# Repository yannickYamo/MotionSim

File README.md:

# MotionSim

MotionSim is an open-source simulator for motor drives. Give it a power transistor from any semiconductor manufacturer, a motor and a load, and it tells you what the part loses, how hot it runs and whether it holds. One physical model covers the whole drive: the switching edges, the losses and the junction temperature, the mains front end, the motor, and the control loop down to its C code.

[Try it in your browser](https://yannickyamo.github.io/MotionSim/): nothing to install, no account, and nothing you enter leaves the page.

## Everything in one place

A drive is usually designed in pieces: a loss calculator from each semiconductor manufacturer, a circuit simulator for the stage, a control toolbox for the loop, and a spreadsheet to hold them together. Each has its own model, and none knows what the others assumed.

MotionSim is one tool and one simulation, from the circuit to the code:

- **Choose the part.** Any manufacturer's transistor, modelled from its own datasheet and compared on your duty.
- **Design the stage.** Losses, junction temperatures, gate drive, DC link and the mains front end.
- **Match the motor.** Seven kinds of motor, each run through its real load from start-up until the heatsink is warm.
- **Find the best control.** Twenty-four schemes, tuned for your motor, simulated switch by switch and compared on what they cost the power stage.
- **Export the code.** The control law as C, checked against the simulation, for your microcontroller.

Change one figure and every answer follows, because it is the same model all the way down.

## The infrastructure

One engine carries a design from the datasheet to the microcontroller. Each layer feeds the next, so a change anywhere moves every answer.

| Layer | What it does |
|---|---|
| **Device models** | Built from the part's own datasheet, each value with its page. IGBT, silicon, SiC and GaN, from any manufacturer, on the same terms. |
| **Loss and thermal engine** | Conduction, switching and junction temperature, solved together, through the application's real duty from start-up until the heatsink is warm. |
| **Front end** | The stage between the mains and the DC link, chosen for the design and counted in its losses. |
| **Control lab** | Twenty-four control schemes, tuned for your motor and simulated switch by switch. |
| **Export** | The control law as C, proved against the simulation, for the microcontroller you pick. |

It runs where you work: in the browser with nothing to install, on your own machine for your own datasheets, from a terminal, or driven by your coding agent.

## The journey

Five steps, one page, the power stage drawn on screen the whole time.

1. **The part.** Drop a datasheet, type a few of its figures, or pick an example.
2. **The motor.** Proposed from the part, yours to change.
3. **The supply.** A battery, a DC supply or the AC mains.
4. **The load.** A washing machine, a compressor, a vehicle, a robot joint, or your own profile.
5. **The answer.** Passes, ruled out, or undecided on this data, with what limits the part and what to change.

From there, open the control lab, close the loop and take the code.

### One design, start to finish

*A 1200 V SiC module, an eight-pole interior-magnet motor, an 800 V battery: can it drive an electric car, and what is the best way to control it?* The part is made up; every figure and graph below is the tool's own.

**1. The verdict.** Passes. At 4500 rpm and 156 N·m the six switches lose 369 W, 220 W of it in switching, at 98.4 % efficiency with the motor's windings. The hottest junction is 82 °C, at standstill, and the part would carry 1.74 times this load.

**2. The drive cycle.** Town, main road, a hill, and town again. The junction is followed through all of it, with the worst swing marked, and braking puts 3.73 MJ back in the battery.

**3. One switching edge.** Press a spike on the loss chart and the turn-off opens as an oscilloscope would show it: 132 A cut off, the voltage overshooting to 895 V on an 800 V link, then ringing out. The turn-on sits beside it, with di/dt, dv/dt and the energy of each.

**4. The control.** The control lab opens on torque control with least current and field weakening, every gain tuned for this motor, and runs it switch by switch. It passes, and points at the switching loss: a modulation that clamps each leg at its current peak would cut it.

**5. A better scheme.** Pick the traction scheme with the clamp placed for least switching loss and run again: 255 W in place of 369 W, the switching loss halved to 113 W and the junction 4 K cooler, with the current's distortion going from 1.77 % to 2.24 %.

**6. The loop, in frequency.** The Laplace lens gives the same loop its Bode plot, margins, step and poles: 62.8° of phase margin, 10 dB of gain margin, a 2.25 kHz bandwidth.

**7. The code.** Export the scheme as C, with a replay that checks it against the run.

## Outcomes

- **A part chosen on your own duty.** Up to five parts, from any manufacturers, side by side.
- **An answer you can stand behind.** Every figure opens on its equation and its datasheet page. Where the datasheet cannot settle it, you are told what to measure.
- **Thermal trouble found before the prototype.** The hottest moment of the real duty, and the life that cycling leaves.
- **A drive, not only a part.** The front end, the tuned control and the C that runs it, from the same design.

## Built for AI agents

MotionSim runs an MCP server beside the page. Connect Claude Code, or any MCP client, and your agent works on the same design you see:

```
claude mcp add --transport http motionsim http://localhost:4310/mcp --header "Authorization: Bearer <code>"
```

- **It reads what you see.** The design, the results, the scheme's blocks and gains, the loop margins and the traces of the last run.
- **It does what you do.** Chooses a part, changes a figure, switches the scheme, retunes a gain, runs a test or a sweep, exports the report and the C.
- **You stay in control.** Every change shows on your page as it happens, with **Undo**, and is listed in the agent's activity.

Ask it to review the design, to tune the current loop for more phase margin, or to find the lowest-loss scheme. The server runs on your machine only. With no page at all, `motionsim agent` prints the guide for driving MotionSim from a terminal. See [docs/MCP.md](https://github.com/yannickYamo/MotionSim/blob/main/docs/MCP.md).

## Your own parts

The live page takes the few figures you type from a datasheet. To have the PDF read for you, and to open the control lab, run MotionSim on your own machine:

```
uvx --from git+https://github.com/yannickYamo/MotionSim motionsim serve
```

The datasheet is read by a language model you choose, with your own key, or by one you host. The project runs no server: your files go from your machine to your model and nowhere else.

From a terminal, with no datasheet and no key:

```
motionsim simulate example --vdc 300 --irms 10 --m 0.9 --pf 0.85 --fsw 8000 --tsink 60
```

```
made-up 600 V IGBT (Si IGBT)
  switch   conduction    4.602 W
           turn-on       0.888 W
           turn-off      0.708 W
  diode    conduction    1.079 W
           recovery      0.286 W
  power-stage loss       45.37 W
  efficiency             98.17 %
  Tj switch  average      80.9 °C   peak   85.4 °C
  Tj diode   average      76.9 °C   peak   79.1 °C
  T case                  64.5 °C
  margin to Tj max        45.3 °C
  hottest junction        76.9 to 104.7 °C across the thermal assumptions
    - heating between chips computed for a generic module, construction not given: 0.21 K/W (0.00 to 0.68) per watt in each other chip
  data support        interpolated
```

[docs/GUIDE.md](https://github.com/yannickYamo/MotionSim/blob/main/docs/GUIDE.md) has Docker, pip, every command, and how a coding agent drives it.

## How it compares

| | Manufacturers' web tools | Circuit simulators | MotionSim |
|---|---|---|---|
| Parts | One manufacturer's | Any, if you build the model | Any manufacturer's, from its datasheet |
| What you give | An operating point | A circuit | A motor, a supply and a load |
| Where the model comes from | Not shown | Entered by hand | Each value with its datasheet page |
| Assumptions and gaps | Not shown | Not shown | Listed in each result |
| Comparing parts | Within one manufacturer | Model by model | Any manufacturers, side by side |
| Accuracy | Calibrated on the manufacturer's own measurements | As good as your model | See below |

## How far to trust it

MotionSim is early and exploratory. The manufacturers' tools and the circuit simulators are ahead on accuracy. Against one manufacturer's simulator on one part, total loss came out 5 to 13% high. Against four published reference designs, loss came out low (10 to 31% on one board) and a board with no heatsink ran up to about twice as warm as measured. Losses use the datasheet's typical values, so a part at the edge of its spread runs hotter than shown.

[docs/VALIDATION.md](https://github.com/yannickYamo/MotionSim/blob/main/docs/VALIDATION.md) has every check, including the ones that fail. [docs/LIMITS.md](https://github.com/yannickYamo/MotionSim/blob/main/docs/LIMITS.md) says what it does not do.

## More

- [docs/GUIDE.md](https://github.com/yannickYamo/MotionSim/blob/main/docs/GUIDE.md): every step, every result, install, the command line and coding agents.
- [docs/CASE_STUDY.md](https://github.com/yannickYamo/MotionSim/blob/main/docs/CASE_STUDY.md): four real datasheets from four manufacturers, from PDF to verdict.
- [docs/DESIGN_DECISIONS.md](https://github.com/yannickYamo/MotionSim/blob/main/docs/DESIGN_DECISIONS.md): the problems it starts from and the trade-offs taken.
- [docs/CONTROL.md](https://github.com/yannickYamo/MotionSim/blob/main/docs/CONTROL.md), [docs/EXPORT_C.md](https://github.com/yannickYamo/MotionSim/blob/main/docs/EXPORT_C.md), [docs/MCP.md](https://github.com/yannickYamo/MotionSim/blob/main/docs/MCP.md), [docs/BOARD.md](https://github.com/yannickYamo/MotionSim/blob/main/docs/BOARD.md), [docs/THERMAL_MODEL.md](https://github.com/yannickYamo/MotionSim/blob/main/docs/THERMAL_MODEL.md): the control lab, the C export, coding agents, board files and the thermal model.
- [docs/ROADMAP.md](https://github.com/yannickYamo/MotionSim/blob/main/docs/ROADMAP.md), [CHANGELOG.md](https://github.com/yannickYamo/MotionSim/blob/main/CHANGELOG.md), [CONTRIBUTING.md](https://github.com/yannickYamo/MotionSim/blob/main/CONTRIBUTING.md), [SECURITY.md](https://github.com/yannickYamo/MotionSim/blob/main/SECURITY.md), [THIRD_PARTY.md](https://github.com/yannickYamo/MotionSim/blob/main/THIRD_PARTY.md), [CITATION.cff](https://github.com/yannickYamo/MotionSim/blob/main/CITATION.cff).

Device data comes only from datasheets you supply. Datasheets are their manufacturers' property: none is distributed here, and no manufacturer's internal data or models are used.

## Author

MotionSim is designed and maintained by Yannick Maurice.

## Disclaimer

MotionSim is an exploratory engineering aid. Its results are estimates built from datasheet values, stated assumptions and simplified models, and they can be wrong.

Do not rely on it alone to design, size or approve hardware. Power electronics can start fires, destroy equipment and injure or kill. Check every result against the manufacturer's data, verify by measurement on real hardware, and follow the safety standards that apply to your product. The authors and contributors accept no responsibility for any design error, damage, injury or loss arising from use of this software. See [DISCLAIMER.md](https://github.com/yannickYamo/MotionSim/blob/main/DISCLAIMER.md).

## Licence

Apache-2.0, which provides the software as is, without warranty and without liability.

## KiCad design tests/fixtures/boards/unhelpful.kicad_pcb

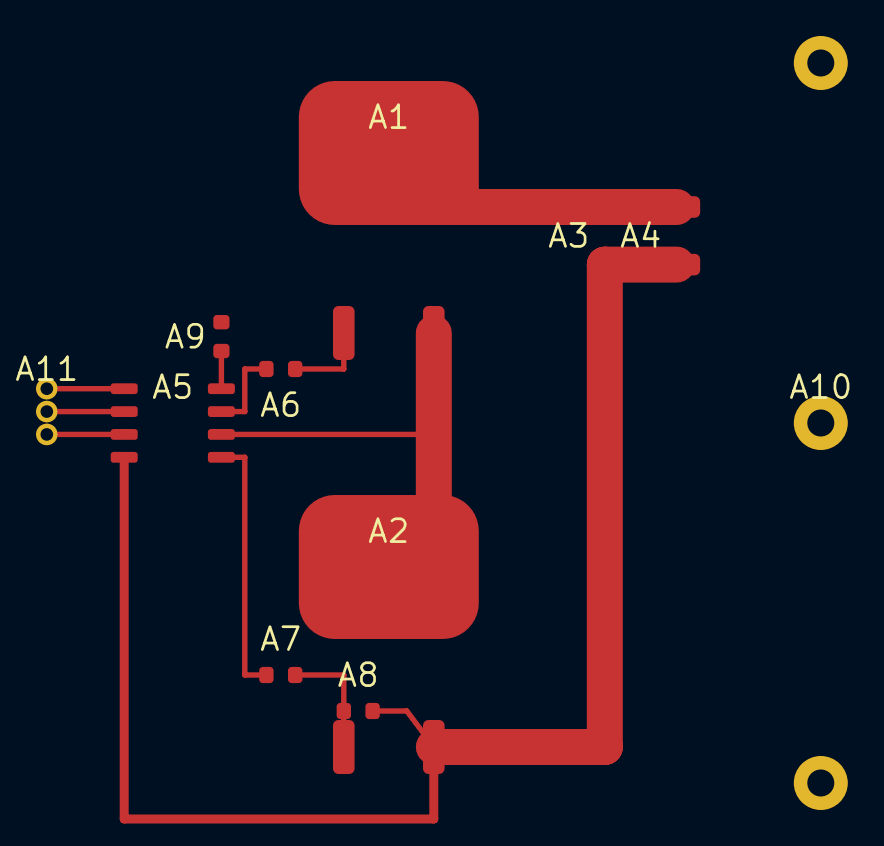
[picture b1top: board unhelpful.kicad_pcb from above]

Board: 2 copper layers, 11 parts (0 on the bottom side), 11 nets.

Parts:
A1, A2: made-up 100 V MOSFET; outline_3
A3, A9: 100n; outline_2
A4: 4.7uF/100V; outline_2
A5: made-up half-bridge driver; outline_8
A6, A7: 10R; outline_2
A8: 10k; outline_2
A10: made-up 3-pin terminal; outline_3
A11: made-up 3-pin header; outline_3

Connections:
unnamed: A1.2, A3.1, A4.1, A10.1
unnamed: A2.3, A3.2, A4.2, A5.4, A8.2, A10.3
unnamed: A1.3, A2.2, A5.6, A9.1, A10.2
unnamed: A1.1, A6.2
unnamed: A2.1, A7.2, A8.1
unnamed: A5.7, A6.1
unnamed: A5.5, A7.1
unnamed: A5.8, A9.2
unnamed: A5.1, A11.1
unnamed: A5.2, A11.2
unnamed: A5.3, A11.3

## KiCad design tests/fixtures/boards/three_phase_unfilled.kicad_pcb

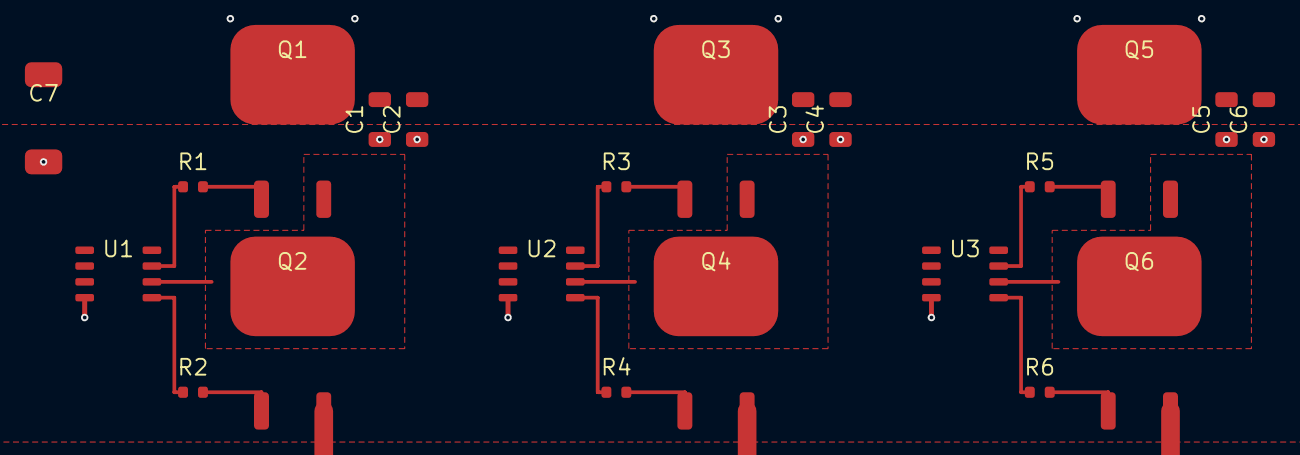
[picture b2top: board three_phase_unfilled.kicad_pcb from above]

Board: 4 copper layers, 22 parts (0 on the bottom side), 18 nets.

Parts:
C1, C2, C3, C4, C5, C6: 1uF/100V; C_1206
C7: 47uF; CP_Elec_8x10
Q1, Q2, Q3, Q4, Q5, Q6: made-up 100 V MOSFET; TO-263-2
R1, R2, R3, R4, R5, R6: 4R7; R_0603
U1, U2, U3: made-up half-bridge driver; SOIC-8

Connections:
GH_U: Q1.1, R1.2
GH_V: Q3.1, R3.2
GH_W: Q5.1, R5.2
GL_U: Q2.1, R2.2
GL_V: Q4.1, R4.2
GL_W: Q6.1, R6.2
GND: C1.2, C2.2, C3.2, C4.2, C5.2, C6.2, C7.2, Q2.3, Q4.3, Q6.3, U1.4, U2.4, U3.4
HO_U: R1.1, U1.7
HO_V: R3.1, U2.7
HO_W: R5.1, U3.7
LO_U: R2.1, U1.5
LO_V: R4.1, U2.5
LO_W: R6.1, U3.5
SW_U: Q1.3, Q2.2, U1.6
SW_V: Q3.3, Q4.2, U2.6
SW_W: Q5.3, Q6.2, U3.6
VBUS: C1.1, C2.1, C3.1, C4.1, C5.1, C6.1, C7.1, Q1.2, Q3.2, Q5.2
VCC: U1.1, U2.1, U3.1

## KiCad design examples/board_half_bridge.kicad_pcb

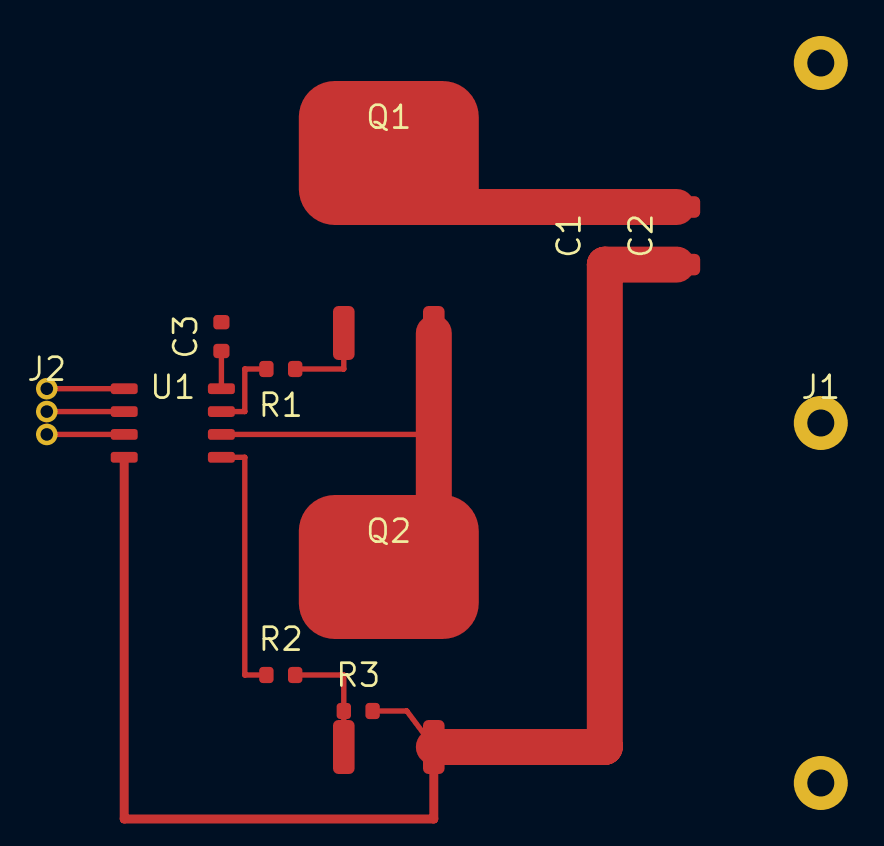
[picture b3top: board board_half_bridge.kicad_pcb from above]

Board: 2 copper layers, 11 parts (0 on the bottom side), 11 nets.

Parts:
C1: 100n; C_1206
C2: 4.7uF/100V; C_1210
C3: 100n; C_0603
J1: made-up 3-pin terminal; Terminal_3
J2: made-up 3-pin header; Header_3
Q1, Q2: made-up 100 V MOSFET; TO-263-2
R1, R2: 10R; R_0603
R3: 10k; R_0603
U1: made-up half-bridge driver; SOIC-8

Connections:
GH: Q1.1, R1.2
GL: Q2.1, R2.2, R3.1
GND: C1.2, C2.2, J1.3, Q2.3, R3.2, U1.4
HIN: J2.2, U1.2
HO: R1.1, U1.7
LIN: J2.3, U1.3
LO: R2.1, U1.5
SW: C3.1, J1.2, Q1.3, Q2.2, U1.6
VB: C3.2, U1.8
VBUS: C1.1, C2.1, J1.1, Q1.2
VCC: J2.1, U1.1
